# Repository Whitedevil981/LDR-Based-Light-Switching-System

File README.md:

# LDR-Based-Light-Switching-System
# Project Objective:
To design a light control system that automatically turns on a street light (or any light source) when it becomes dark and turns it off when there is sufficient daylight, using an LDR (Light Dependent Resistor) and basic electronic components.
# Working Principle:
The system is based on the light-sensing capability of an LDR. An LDR changes its resistance based on the intensity of light falling on it:

Bright light = low resistance

Darkness = high resistance

This change in resistance alters the voltage in a voltage divider circuit, which is used to switch a transistor. The transistor acts as an electronic switch to turn a relay or LED on or off.
# What the Basic PBC Circuit Includes:

LDR as light sensor

LED/light bulb

Resistors 

Power supply (Battery)

Switch 

# Applications:

Street lighting automation

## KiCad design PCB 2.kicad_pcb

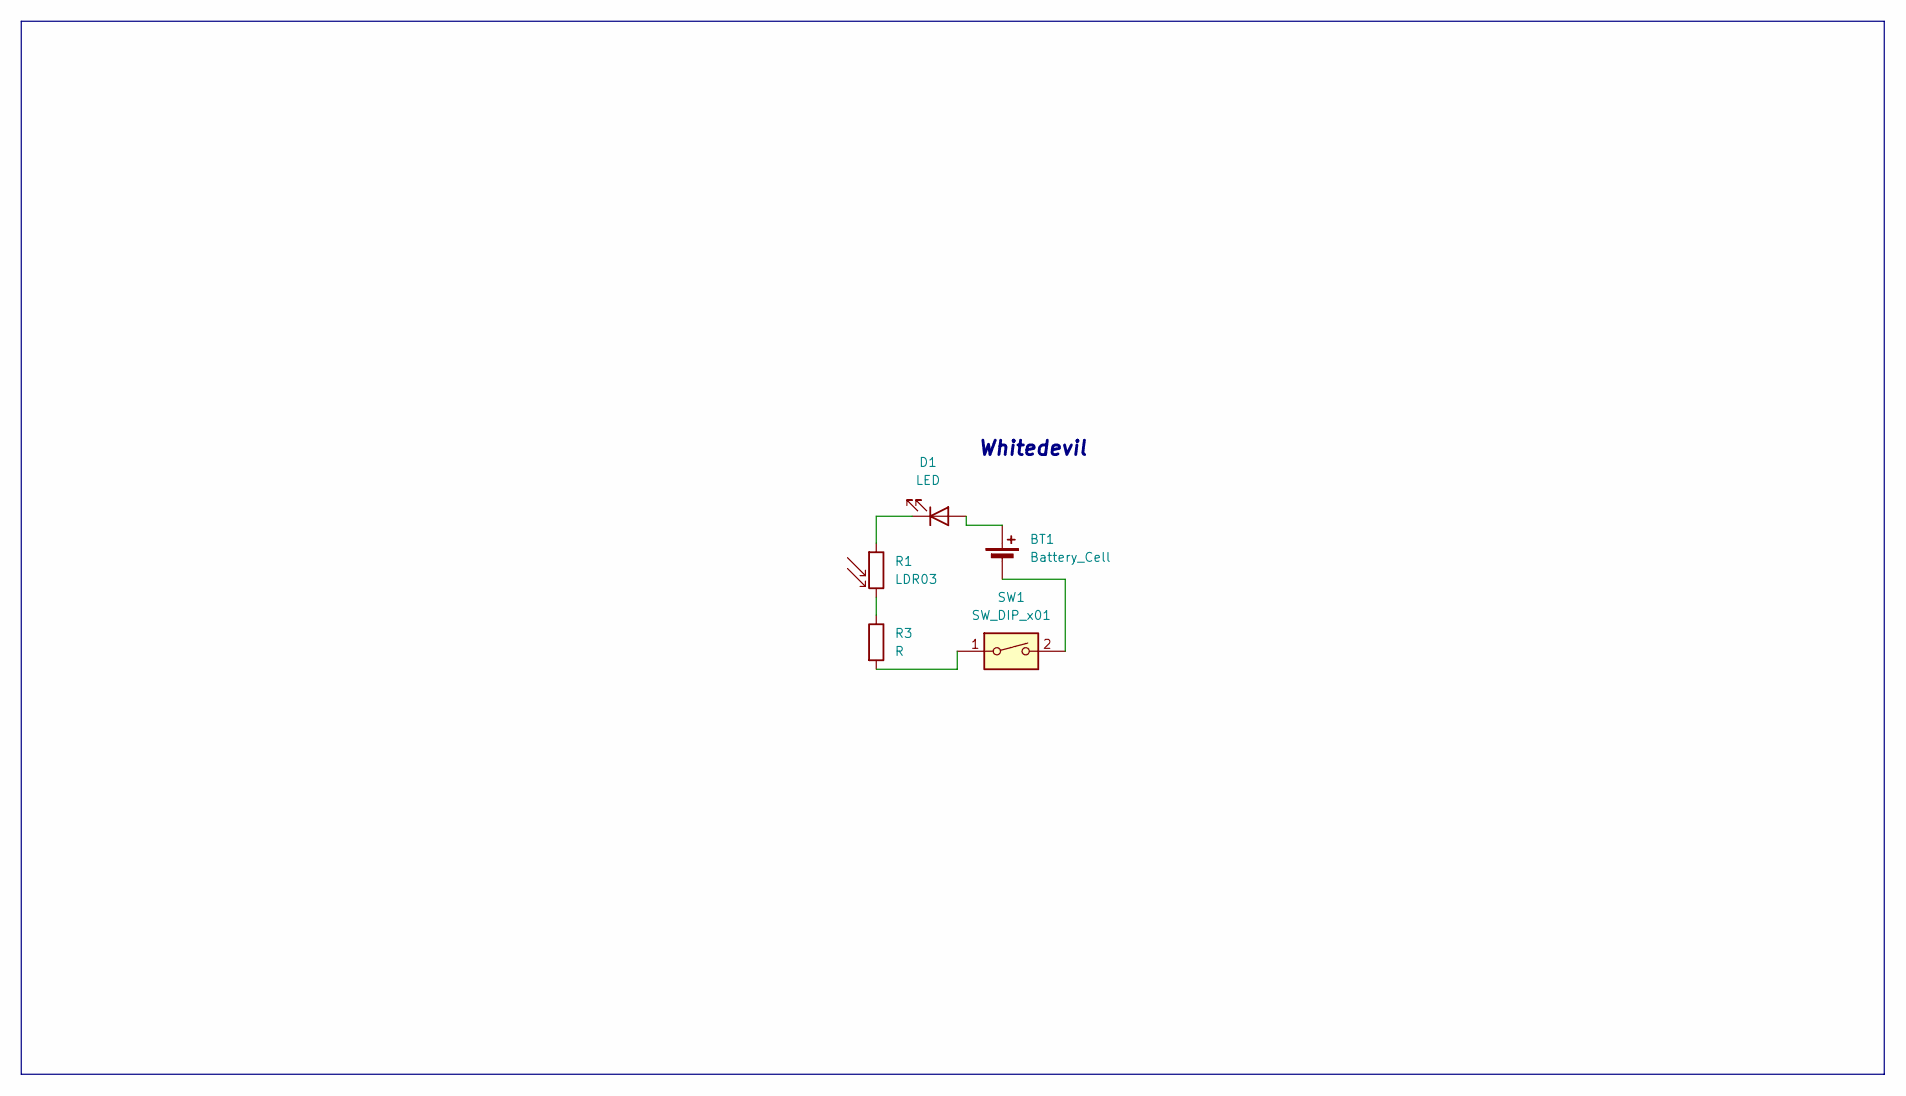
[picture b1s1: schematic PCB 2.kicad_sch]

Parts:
BT1: Battery_Cell; BatteryHolder_Keystone_3034_1x20mm
D1: LED; LED_D5.0mm
R1: LDR03; R_LDR_7x6mm_P5.1mm_Vertical
R3: R; R_Axial_DIN0204_L3.6mm_D1.6mm_P5.08mm_Horizontal
SW1: SW_DIP_x01; SW_PUSH_6mm

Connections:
unnamed: BT1.1 (+), D1.2 (A)
unnamed: BT1.2 (-), SW1.2
unnamed: D1.1 (K), R1.1
unnamed: R1.2, R3.1
unnamed: R3.2, SW1.1

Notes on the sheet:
Whitedevil

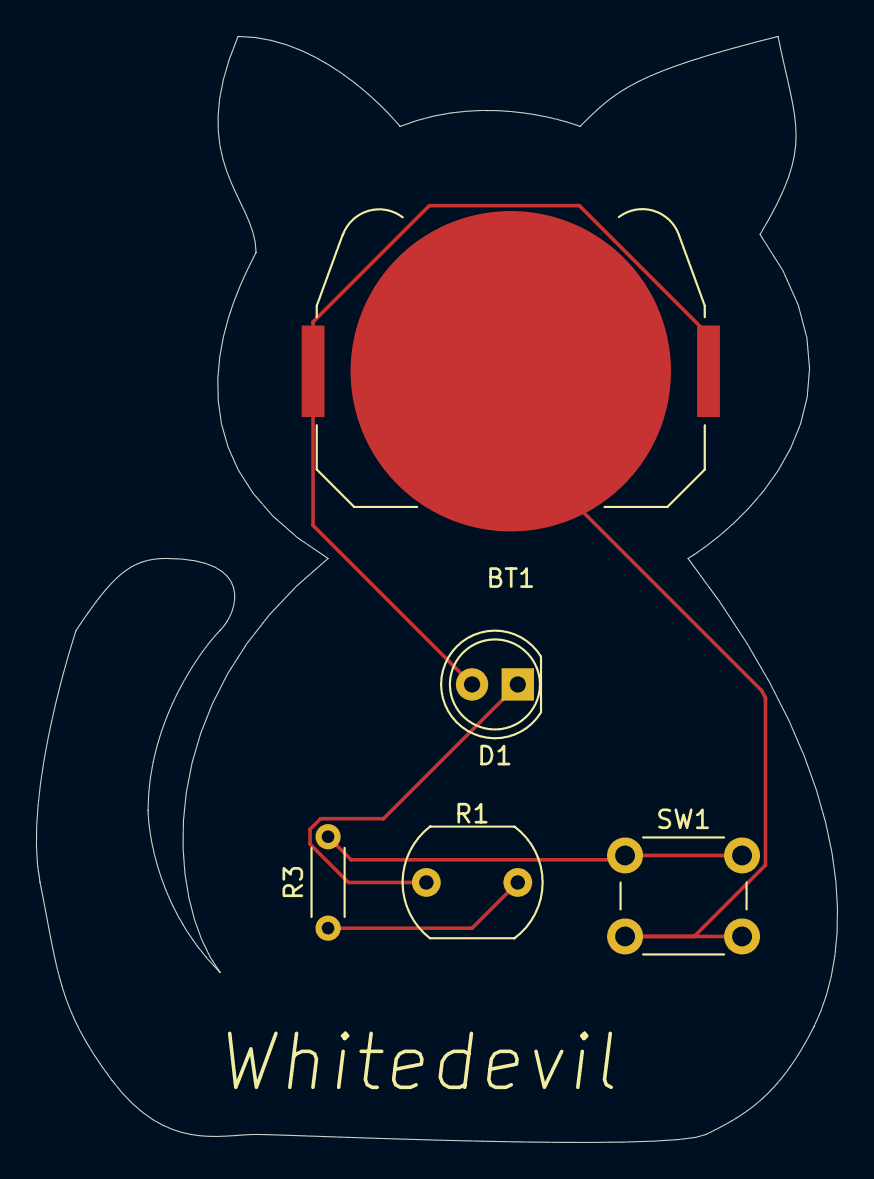
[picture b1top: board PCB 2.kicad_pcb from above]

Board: 2 copper layers, 44.5 x 61.4 mm, 5 parts (0 on the bottom side), 5 nets.

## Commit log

2025-05-08 Create production
